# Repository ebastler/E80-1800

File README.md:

# E80-1800
QMK compatible USB-C PCB for a Cherry G80-1800

The board has been prototyped and works as intended, while fitting most G80-1800 housings. Rev 1.1 and later should fix all tolerance issues, and fit all G80-1800 (and as far as I know also G81-1800) enclosures. I can, however, not guarantee perfect operation of the PCB or compatibility with every enclosure variation - if you encounter any issues, please let me know. Rev 1.2 has not yet been tested, but changes were minimal - no issues are to be expected. Stock situations as well as component rotations at JLC may change over time and hence I can not guarantee for the BOM/CPL files to work perfectly. Please double-check before ordering!

|||
|:----------------------------------------:|:----------------------------------------:|

## Order information at JLCPCB
All relevant files can be found in `E80-1800-pcb-universal\jlcpcb`. The `gerber` subfolder contains a .zip file, the `assembly` subfolder contains the BOM and POS/CPL files needed for assembly. Please double-check all component values and rotations before ordering!

* [gerber](E80-1800-pcb-universal/jlcpcb/gerber/GERBER-E80-1800-pcb-universal.zip)
* [BOM](E80-1800-pcb-universal/jlcpcb/assembly/BOM-E80-1800-pcb-universal.csv)
* [POS](E80-1800-pcb-universal/jlcpcb/assembly/POS-E80-1800-pcb-universal.csv)

Since jlcpcb usually fails to auto-determine the PCB dimensions: `382 x 160 mm` is the correct size.

Consider donating me a few bucks if you order boards :)

## Features
 - USB-C (you have to widen the cable hole in the case with a file or similar)
 - Full ESD protection
 - Future-proof STM32F072 with QMK
 - Optional I²C OLED screen in the card-reader-hole on card-reader G80-1800 models
 - SPI header for Bluetooth LE - software support may or may not follow (currently not supported by QMK). The SPI pads can also be used for other expansions such as adding a Solenoid or RGB stripe.
 - Header to connect an optional battery management daughterboard
 - Single color dimmable backlight (3mm LEDs)
 - Silkscreen labels for LED polarity and multi-layout options for easier assembly

The board is fully supported by the QMK master branch: https://github.com/qmk/qmk_firmware/tree/master/keyboards/ebastler/e80_1800
A VIA compatible JSON file can be found in the "VIA" folder of this repo, and the PCB is also fully supported by https://remap-keys.app

## Supported layouts
The PCB was designed to support all layout options G80-1800 and G81-1800 were originally available in. I did not include layout options that go beyond those on purpose, since overlapping switch holes lead to wobbly switches (remember, the G80 boards are plateless!) which diminishes the typing experience. 
 - Full ISO and ANSI support
 - 1 - 1 - 1 - 6 - 1 - 1 - 1 - 1 bottom row (with flipped or regular spacebar)
 - 1.5 - 1.5 - 7 - 1.5 - 1.5 bottom row
 - Stepped and regular caps lock

## Thanks to
 - [Evy](https://github.com/evyd13) for supplying me with her [GH80-1800 drop in replacement PCB](https://geekhack.org/index.php?topic=96692.0) layout, which I could use for dimensions and measurements - saved me a lot of time! Even if I ended up redrawing the dimensions from scratch and changing a few, being able to use his as a starting point was a lot of help.
 - SMOKEY for motivating me once I lost the will to continue with the project
 - MarvFPV for helping me with the physical PCB dimensions and supplying me with valuable ideas
 - Zitres for organizing and shipping a small-batch closed GB together with me that led to a lot of satisfied users

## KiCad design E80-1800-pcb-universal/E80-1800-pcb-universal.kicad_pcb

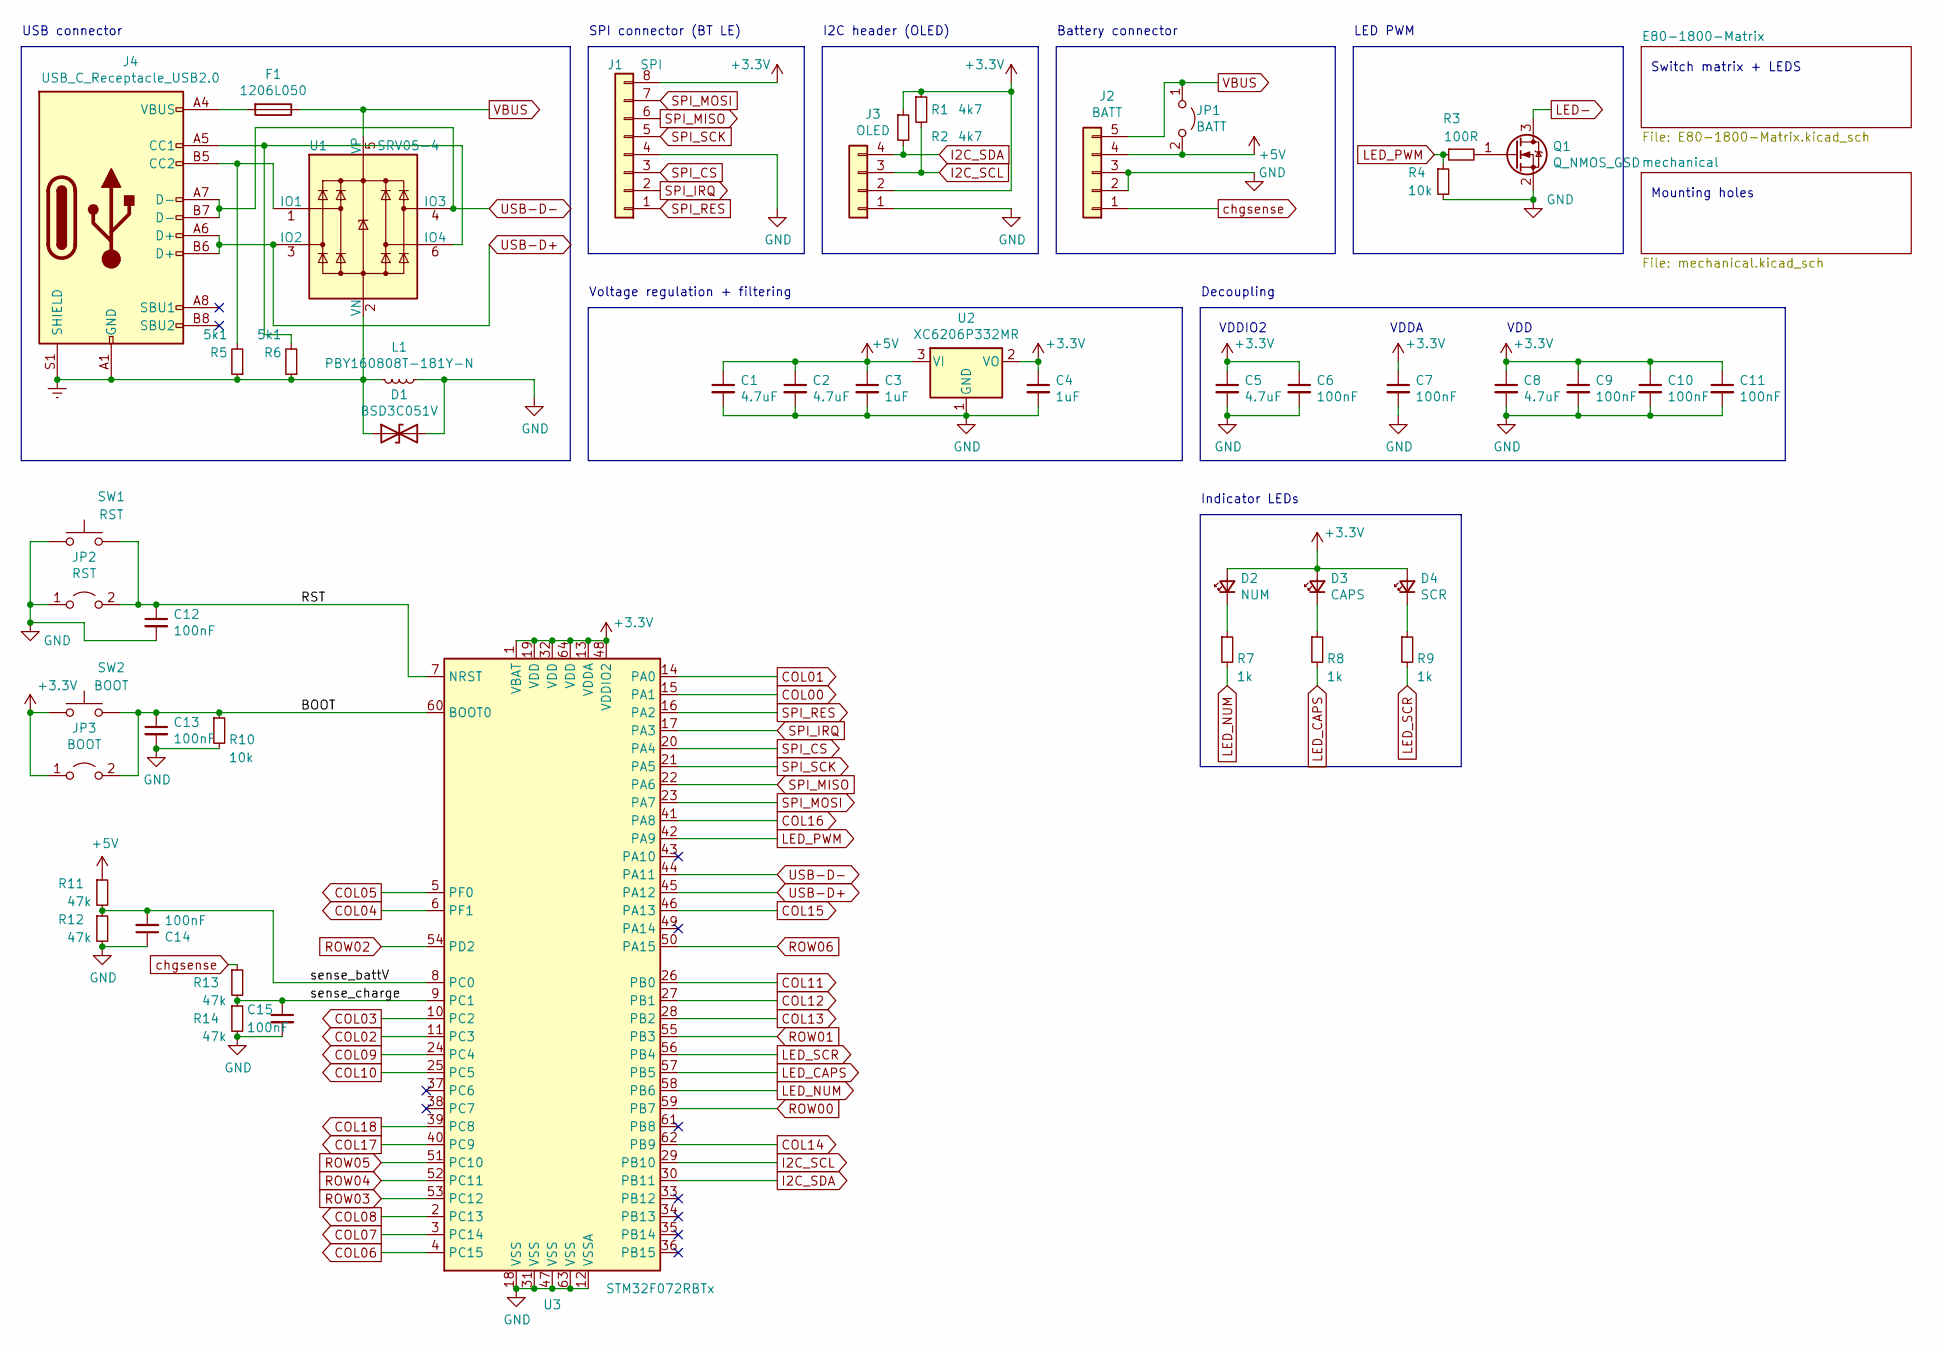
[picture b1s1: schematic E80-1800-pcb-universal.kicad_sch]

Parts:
C1, C2, C5, C8: 4.7uF; C_0603_1608Metric; LCSC C19666
C3, C4: 1uF; C_0603_1608Metric; LCSC C15849
C6, C7, C9, C10, C11, C12, C13, C14, C15: 100nF; C_0603_1608Metric; LCSC C14663
D1: BSD3C051V; D_SOD-323; LCSC C151996
D2: NUM; LED_D3.0mm
D3: CAPS; LED_D3.0mm
D4: SCR; LED_D3.0mm
F1: 1206L050; Fuse_1206_3216Metric; LCSC C151162
J1: SPI; JST_SH_SM08B-SRSS-TB_1x08-1MP_P1.00mm_Horizontal
J2: BATT; JST_SH_SM05B-SRSS-TB_1x05-1MP_P1.00mm_Horizontal
J3: OLED; PinHeader_1x04_P2.54mm_Vertical
J4: USB_C_Receptacle_USB2.0; USB_C_Receptacle_HRO_TYPE-C-31-M-12; LCSC C165948
JP1: BATT; SolderJumper-2_P1.3mm_Bridged2Bar_Pad1.0x1.5mm
JP2: RST; PinHeader_1x02_P2.54mm_Vertical
JP3: BOOT; PinHeader_1x02_P2.54mm_Vertical
L1: PBY160808T-181Y-N; L_0603_1608Metric_Pad1.05x0.95mm_HandSolder; LCSC C114288
Q1: Q_NMOS_GSD; SOT-23; LCSC C20917
R1, R2: 4k7; R_0603_1608Metric; LCSC C23162
R3: 100R; R_0603_1608Metric; LCSC C22775
R4, R10: 10k; R_0603_1608Metric; LCSC C25804
R5, R6: 5k1; R_0603_1608Metric; LCSC C23186
R7, R8, R9: 1k; R_0603_1608Metric; LCSC C21190
R11, R12, R13, R14: 47k; R_0603_1608Metric; LCSC C25819
SW1: RST; SW_SPST_SKQG_WithoutStem
SW2: BOOT; SW_SPST_SKQG_WithoutStem
U1: SRV05-4; SOT-23-6; LCSC C85364
U2: XC6206P332MR; SOT-23; LCSC C5446
U3: STM32F072RBTx; LQFP-64_10x10mm_P0.5mm; LCSC C46046

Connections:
COL00: U3.15 (PA1); also elsewhere on the board
COL01: U3.14 (PA0); also elsewhere on the board
COL02: U3.11 (PC3); also elsewhere on the board
COL03: U3.10 (PC2); also elsewhere on the board
COL04: U3.6 (PF1); also elsewhere on the board
COL05: U3.5 (PF0); also elsewhere on the board
COL06: U3.4 (PC15); also elsewhere on the board
COL07: U3.3 (PC14); also elsewhere on the board
COL08: U3.2 (PC13); also elsewhere on the board
COL09: U3.24 (PC4); also elsewhere on the board
COL10: U3.25 (PC5); also elsewhere on the board
COL11: U3.26 (PB0); also elsewhere on the board
COL12: U3.27 (PB1); also elsewhere on the board
COL13: U3.28 (PB2); also elsewhere on the board
COL14: U3.62 (PB9); also elsewhere on the board
COL15: U3.46 (PA13); also elsewhere on the board
COL16: U3.41 (PA8); also elsewhere on the board
COL17: U3.40 (PC9); also elsewhere on the board
COL18: U3.39 (PC8); also elsewhere on the board
Earth: D1.1 (A1), J4.A1 (GND), J4.A12 (GND), J4.B1 (GND), J4.B12 (GND), J4.S1 (SHIELD), L1.2, R5.1, R6.1, U1.2 (VN)
I2C_SCL: J3.3, R1.2, U3.29 (PB10)
I2C_SDA: J3.4, R2.2, U3.30 (PB11)
LED-: Q1.3 (D); also elsewhere on the board
LED_CAPS: R8.2, U3.57 (PB5)
LED_NUM: R7.2, U3.58 (PB6)
LED_PWM: R3.1, R4.1, U3.42 (PA9)
LED_SCR: R9.2, U3.56 (PB4)
unnamed: D2.1 (K), R7.1
unnamed: D3.1 (K), R8.1
unnamed: D4.1 (K), R9.1
unnamed: F1.2, J4.A4 (VBUS), J4.A9 (VBUS), J4.B4 (VBUS), J4.B9 (VBUS)
unnamed: J4.A5 (CC1), R6.2, U1.6 (IO4)
unnamed: J4.B5 (CC2), R5.2, U1.1 (IO1)
unnamed: Q1.1 (G), R3.2
ROW00: U3.59 (PB7); also elsewhere on the board
ROW01: U3.55 (PB3); also elsewhere on the board
ROW02: U3.54 (PD2); also elsewhere on the board
ROW03: U3.53 (PC12); also elsewhere on the board
ROW04: U3.52 (PC11); also elsewhere on the board
ROW05: U3.51 (PC10); also elsewhere on the board
ROW06: U3.50 (PA15); also elsewhere on the board
SPI_CS: J1.3, U3.20 (PA4)
SPI_IRQ: J1.2, U3.17 (PA3)
SPI_MISO: J1.6, U3.22 (PA6)
SPI_MOSI: J1.7, U3.23 (PA7)
SPI_RES: J1.1, U3.16 (PA2)
SPI_SCK: J1.5, U3.21 (PA5)
USB-D+: J4.A6 (D+), J4.B6 (D+), U1.3 (IO2), U3.45 (PA12)
USB-D-: J4.A7 (D-), J4.B7 (D-), U1.4 (IO3), U3.44 (PA11)
VBUS: F1.1, J2.5, JP1.1 (A), U1.5 (VP)
chgsense: J2.1, R13.1

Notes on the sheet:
Mounting holes
LED PWM
VDDA
SPI connector (BT LE)
VDD
USB connector
I2C header (OLED)
VDDIO2
Indicator LEDs
Voltage regulation + filtering
Switch matrix + LEDS
Decoupling
Battery connector

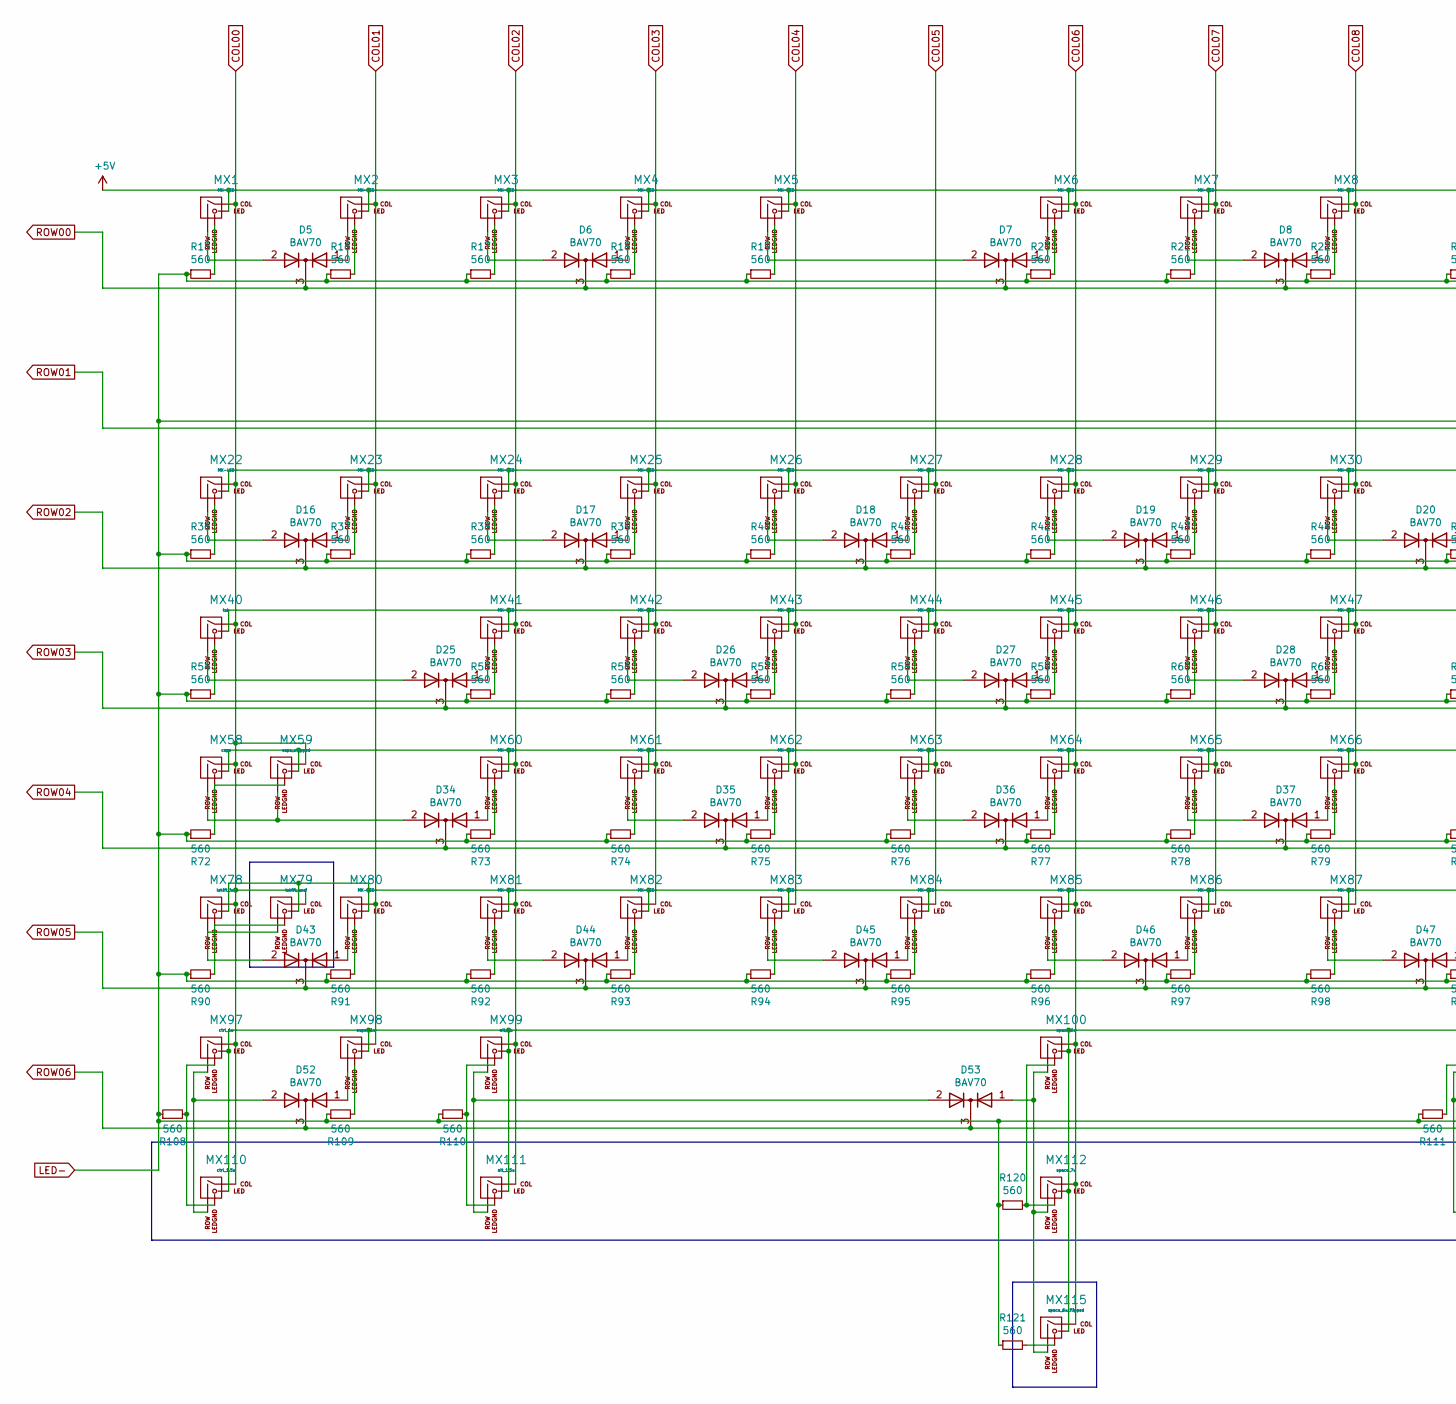
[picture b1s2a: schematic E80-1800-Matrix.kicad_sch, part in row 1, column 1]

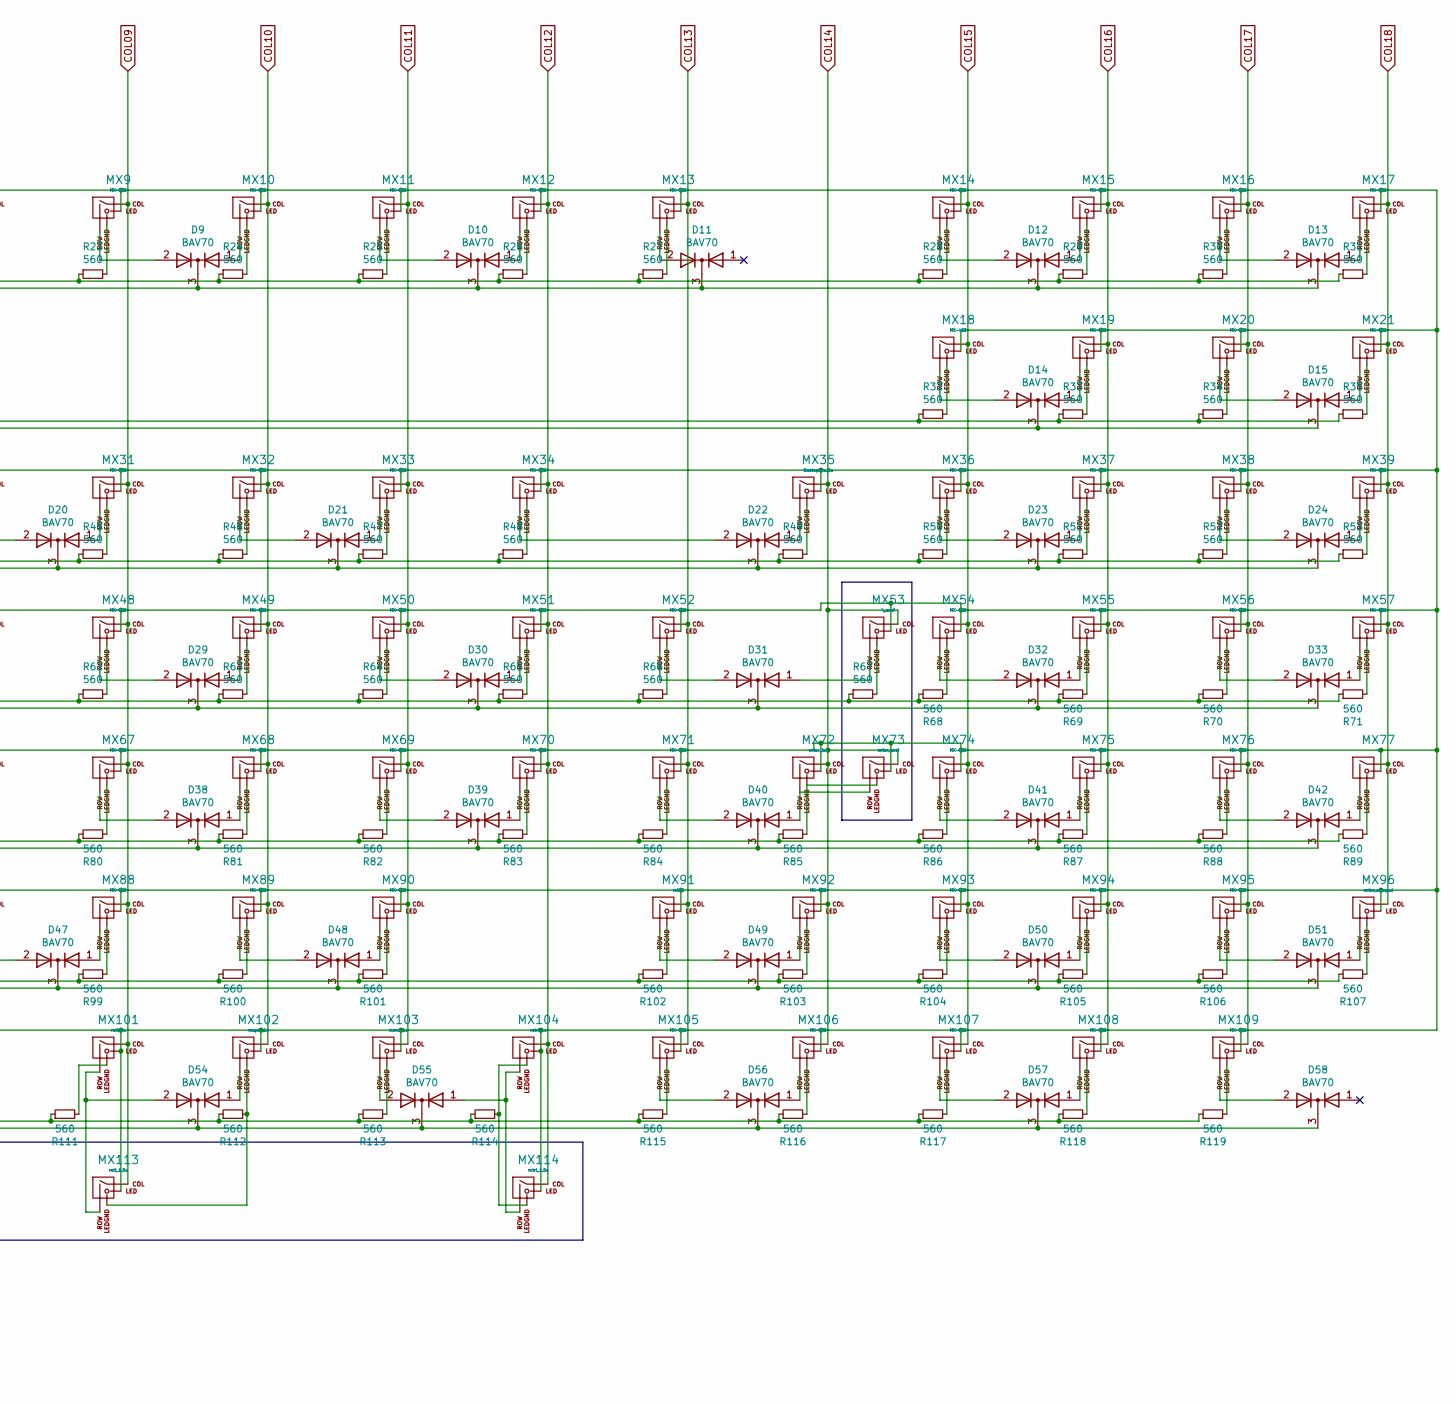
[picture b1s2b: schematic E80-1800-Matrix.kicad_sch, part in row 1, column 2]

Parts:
D5, D6, D7, D8, D9, D10, D11, D12, D13, D14, D15, D16, D17, D18, D19, D20, D21, D22, D23, D24, D25, D26, D27, D28, D29, D30, D31, D32, D33, D34, D35, D36, D37, D38, D39, D40, D41, D42, D43, D44, D45, D46, D47, D48, D49, D50, D51, D52, D53, D54, D55, D56, D57, D58: BAV70; SOT-23; LCSC C68978
MX1, MX2, MX3, MX4, MX5, MX6, MX7, MX8, MX9, MX10, MX11, MX12, MX13, MX14, MX15, MX16, MX17, MX18, MX19, MX20, MX21, MX22, MX23, MX24, MX25, MX26, MX27, MX28, MX29, MX30, MX31, MX32, MX33, MX34, MX36, MX37, MX38, MX39, MX41, MX42, MX43, MX44, MX45, MX46, MX47, MX48, MX49, MX50, MX51, MX52, MX54, MX55, MX56, MX57, MX60, MX61, MX62, MX63, MX64, MX65, MX66, MX67, MX68, MX69, MX70, MX71, MX74, MX75, MX76, MX80, MX81, MX82, MX83, MX84, MX85, MX86, MX87, MX88, MX89, MX90, MX92, MX93, MX94, MX95, MX105, MX106, MX107, MX108, MX109: MX-LED; MXOnly-1U
MX35: Backspace_2u; MXOnly-2U
MX40: tab; MXOnly-1.5U
MX53: \_ansi; MXOnly-1.5U
MX58: caps; MXOnly-1.75U-FLIPPED
MX59: caps_stepped; MXOnly-1.25U
MX72: enter_iso; MXOnly-ISO-ROTATED-ReversedStabilizers
MX73: enter_ansi; MXOnly-2.25U
MX77: +; MXOnly-1U
MX78: lshift_iso; MXOnly-1.25U
MX79: lshift_ansi; MXOnly-2.25U
MX91: rshift; MXOnly-1.75U
MX96: enter_numpad; MXOnly-ISO
MX97: ctrl_1u; MXOnly-1U
MX98: super_1u; MXOnly-1U
MX99: alt_1u; MXOnly-1U-FLIPPED
MX100: space_6u; MXOnly-6U
MX101: ralt_1u; MXOnly-1U
MX102: rsuper_1u; MXOnly-1U
MX103: menu_1u; MXOnly-1U
MX104: rctrl_1u; MXOnly-1U-FLIPPED
MX110: ctrl_1.5u; MXOnly-1.5U-FLIPPED
MX111: alt_1.5u; MXOnly-1.5U
MX112: space_7u; MXOnly-7U
MX113: ralt_1.5u; MXOnly-1.5U-FLIPPED
MX114: rctrl_1.5u; MXOnly-1.5U
MX115: space_6u_flipped; MXOnly-1U
R15, R16, R17, R18, R19, R20, R21, R22, R23, R24, R25, R26, R27, R28, R29, R30, R31, R32, R33, R34, R35, R36, R37, R38, R39, R40, R41, R42, R43, R44, R45, R46, R47, R48, R49, R50, R51, R52, R53, R54, R55, R56, R57, R58, R59, R60, R61, R62, R63, R64, R65, R66, R67, R68, R69, R70, R71, R72, R73, R74, R75, R76, R77, R78, R79, R80, R81, R82, R83, R84, R85, R86, R87, R88, R89, R90, R91, R92, R93, R94, R95, R96, R97, R98, R99, R100, R101, R102, R103, R104, R105, R106, R107, R108, R109, R110, R111, R112, R113, R114, R115, R116, R117, R118, R119, R120, R121: 560; R_0603_1608Metric; LCSC C23204

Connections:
COL00: MX1.1 (COL), MX22.1 (COL), MX40.1 (COL), MX58.1 (COL), MX59.1 (COL), MX78.1 (COL), MX79.1 (COL), MX97.1 (COL), MX110.1 (COL); also elsewhere on the board
COL01: MX2.1 (COL), MX23.1 (COL), MX80.1 (COL), MX98.1 (COL); also elsewhere on the board
COL02: MX3.1 (COL), MX24.1 (COL), MX41.1 (COL), MX60.1 (COL), MX81.1 (COL), MX99.1 (COL), MX111.1 (COL); also elsewhere on the board
COL03: MX4.1 (COL), MX25.1 (COL), MX42.1 (COL), MX61.1 (COL), MX82.1 (COL); also elsewhere on the board
COL04: MX5.1 (COL), MX26.1 (COL), MX43.1 (COL), MX62.1 (COL), MX83.1 (COL); also elsewhere on the board
COL05: MX27.1 (COL), MX44.1 (COL), MX63.1 (COL), MX84.1 (COL); also elsewhere on the board
COL06: MX6.1 (COL), MX28.1 (COL), MX45.1 (COL), MX64.1 (COL), MX85.1 (COL), MX100.1 (COL), MX112.1 (COL), MX115.1 (COL); also elsewhere on the board
COL07: MX7.1 (COL), MX29.1 (COL), MX46.1 (COL), MX65.1 (COL), MX86.1 (COL); also elsewhere on the board
COL08: MX8.1 (COL), MX30.1 (COL), MX47.1 (COL), MX66.1 (COL), MX87.1 (COL); also elsewhere on the board
COL09: MX9.1 (COL), MX31.1 (COL), MX48.1 (COL), MX67.1 (COL), MX88.1 (COL), MX101.1 (COL), MX113.1 (COL); also elsewhere on the board
COL10: MX10.1 (COL), MX32.1 (COL), MX49.1 (COL), MX68.1 (COL), MX89.1 (COL), MX102.1 (COL); also elsewhere on the board
COL11: MX11.1 (COL), MX33.1 (COL), MX50.1 (COL), MX69.1 (COL), MX90.1 (COL), MX103.1 (COL); also elsewhere on the board
COL12: MX12.1 (COL), MX34.1 (COL), MX51.1 (COL), MX70.1 (COL), MX104.1 (COL), MX114.1 (COL); also elsewhere on the board
COL13: MX13.1 (COL), MX52.1 (COL), MX71.1 (COL), MX91.1 (COL), MX105.1 (COL); also elsewhere on the board
COL14: MX35.1 (COL), MX53.1 (COL), MX72.1 (COL), MX73.1 (COL), MX92.1 (COL), MX106.1 (COL); also elsewhere on the board
COL15: MX14.1 (COL), MX18.1 (COL), MX36.1 (COL), MX54.1 (COL), MX74.1 (COL), MX93.1 (COL), MX107.1 (COL); also elsewhere on the board
COL16: MX15.1 (COL), MX19.1 (COL), MX37.1 (COL), MX55.1 (COL), MX75.1 (COL), MX94.1 (COL), MX108.1 (COL); also elsewhere on the board
COL17: MX16.1 (COL), MX20.1 (COL), MX38.1 (COL), MX56.1 (COL), MX76.1 (COL), MX95.1 (COL), MX109.1 (COL); also elsewhere on the board
COL18: MX17.1 (COL), MX21.1 (COL), MX39.1 (COL), MX57.1 (COL), MX77.1 (COL), MX96.1 (COL); also elsewhere on the board
LED-: R15.1, R16.1, R17.1, R18.1, R19.1, R20.1, R21.1, R22.1, R23.1, R24.1, R25.1, R26.1, R27.1, R28.1, R29.1, R30.1, R31.1, R32.1, R33.1, R34.1, R35.1, R36.1, R37.1, R38.1, R39.1, R40.1, R41.1, R42.1, R43.1, R44.1, R45.1, R46.1, R47.1, R48.1, R49.1, R50.1, R51.1, R52.1, R53.1, R54.1, R55.1, R56.1, R57.1, R58.1, R59.1, R60.1, R61.1, R62.1, R63.1, R64.1, R65.1, R66.1, R67.1, R68.1, R69.1, R70.1, R71.1, R72.1, R73.1, R74.1, R75.1, R76.1, R77.1, R78.1, R79.1, R80.1, R81.1, R82.1, R83.1, R84.1, R85.1, R86.1, R87.1, R88.1, R89.1, R90.1, R91.1, R92.1, R93.1, R94.1, R95.1, R96.1, R97.1, R98.1, R99.1, R100.1, R101.1, R102.1, R103.1, R104.1, R105.1, R106.1, R107.1, R108.1, R109.1, R110.1, R111.1, R112.1, R113.1, R114.1, R115.1, R116.1, R117.1, R118.1, R119.1, R120.1, R121.1; also elsewhere on the board
unnamed: D5.1 (A), MX2.2 (ROW)
unnamed: D5.2 (A), MX1.2 (ROW)
unnamed: D6.1 (A), MX4.2 (ROW)
unnamed: D6.2 (A), MX3.2 (ROW)
unnamed: D7.1 (A), MX6.2 (ROW)
unnamed: D7.2 (A), MX5.2 (ROW)
unnamed: D8.1 (A), MX8.2 (ROW)
unnamed: D8.2 (A), MX7.2 (ROW)
unnamed: D9.1 (A), MX10.2 (ROW)
unnamed: D9.2 (A), MX9.2 (ROW)
unnamed: D10.1 (A), MX12.2 (ROW)
unnamed: D10.2 (A), MX11.2 (ROW)
unnamed: D11.2 (A), MX13.2 (ROW)
unnamed: D12.1 (A), MX15.2 (ROW)
unnamed: D12.2 (A), MX14.2 (ROW)
unnamed: D13.1 (A), MX17.2 (ROW)
unnamed: D13.2 (A), MX16.2 (ROW)
unnamed: D14.1 (A), MX19.2 (ROW)
unnamed: D14.2 (A), MX18.2 (ROW)
unnamed: D15.1 (A), MX21.2 (ROW)
unnamed: D15.2 (A), MX20.2 (ROW)
unnamed: D16.1 (A), MX23.2 (ROW)
unnamed: D16.2 (A), MX22.2 (ROW)
unnamed: D17.1 (A), MX25.2 (ROW)
unnamed: D17.2 (A), MX24.2 (ROW)
unnamed: D18.1 (A), MX27.2 (ROW)
unnamed: D18.2 (A), MX26.2 (ROW)
unnamed: D19.1 (A), MX29.2 (ROW)
unnamed: D19.2 (A), MX28.2 (ROW)
unnamed: D20.1 (A), MX31.2 (ROW)
unnamed: D20.2 (A), MX30.2 (ROW)
unnamed: D21.1 (A), MX33.2 (ROW)
unnamed: D21.2 (A), MX32.2 (ROW)
unnamed: D22.1 (A), MX35.2 (ROW)
unnamed: D22.2 (A), MX34.2 (ROW)
unnamed: D23.1 (A), MX37.2 (ROW)
unnamed: D23.2 (A), MX36.2 (ROW)
unnamed: D24.1 (A), MX39.2 (ROW)
unnamed: D24.2 (A), MX38.2 (ROW)
unnamed: D25.1 (A), MX41.2 (ROW)
unnamed: D25.2 (A), MX40.2 (ROW)
unnamed: D26.1 (A), MX43.2 (ROW)
unnamed: D26.2 (A), MX42.2 (ROW)
unnamed: D27.1 (A), MX45.2 (ROW)
unnamed: D27.2 (A), MX44.2 (ROW)
unnamed: D28.1 (A), MX47.2 (ROW)
unnamed: D28.2 (A), MX46.2 (ROW)
unnamed: D29.1 (A), MX49.2 (ROW)
unnamed: D29.2 (A), MX48.2 (ROW)
unnamed: D30.1 (A), MX51.2 (ROW)
unnamed: D30.2 (A), MX50.2 (ROW)
unnamed: D31.1 (A), MX53.2 (ROW)
unnamed: D31.2 (A), MX52.2 (ROW)
unnamed: D32.1 (A), MX55.2 (ROW)
unnamed: D32.2 (A), MX54.2 (ROW)
unnamed: D33.1 (A), MX57.2 (ROW)
unnamed: D33.2 (A), MX56.2 (ROW)
unnamed: D34.1 (A), MX60.2 (ROW)
unnamed: D34.2 (A), MX58.2 (ROW), MX59.2 (ROW)
unnamed: D35.1 (A), MX62.2 (ROW)
unnamed: D35.2 (A), MX61.2 (ROW)
unnamed: D36.1 (A), MX64.2 (ROW)
unnamed: D36.2 (A), MX63.2 (ROW)
unnamed: D37.1 (A), MX66.2 (ROW)
unnamed: D37.2 (A), MX65.2 (ROW)
unnamed: D38.1 (A), MX68.2 (ROW)
unnamed: D38.2 (A), MX67.2 (ROW)
unnamed: D39.1 (A), MX70.2 (ROW)
unnamed: D39.2 (A), MX69.2 (ROW)
unnamed: D40.1 (A), MX72.2 (ROW), MX73.2 (ROW)
unnamed: D40.2 (A), MX71.2 (ROW)
unnamed: D41.1 (A), MX75.2 (ROW)
unnamed: D41.2 (A), MX74.2 (ROW)
unnamed: D42.1 (A), MX77.2 (ROW)
unnamed: D42.2 (A), MX76.2 (ROW)
unnamed: D43.1 (A), MX80.2 (ROW)
unnamed: D43.2 (A), MX78.2 (ROW), MX79.2 (ROW)
unnamed: D44.1 (A), MX82.2 (ROW)
unnamed: D44.2 (A), MX81.2 (ROW)
unnamed: D45.1 (A), MX84.2 (ROW)
unnamed: D45.2 (A), MX83.2 (ROW)
unnamed: D46.1 (A), MX86.2 (ROW)
unnamed: D46.2 (A), MX85.2 (ROW)
unnamed: D47.1 (A), MX88.2 (ROW)
unnamed: D47.2 (A), MX87.2 (ROW)
unnamed: D48.1 (A), MX90.2 (ROW)
unnamed: D48.2 (A), MX89.2 (ROW)
unnamed: D49.1 (A), MX92.2 (ROW)
unnamed: D49.2 (A), MX91.2 (ROW)
unnamed: D50.1 (A), MX94.2 (ROW)
unnamed: D50.2 (A), MX93.2 (ROW)
unnamed: D51.1 (A), MX96.2 (ROW)
unnamed: D51.2 (A), MX95.2 (ROW)
unnamed: D52.1 (A), MX98.2 (ROW)
unnamed: D52.2 (A), MX97.2 (ROW), MX110.2 (ROW)
unnamed: D53.1 (A), MX100.2 (ROW), MX112.2 (ROW), MX115.2 (ROW)
unnamed: D53.2 (A), MX99.2 (ROW), MX111.2 (ROW)
unnamed: D54.1 (A), MX102.2 (ROW)
unnamed: D54.2 (A), MX101.2 (ROW), MX113.2 (ROW)
unnamed: D55.1 (A), MX104.2 (ROW), MX114.2 (ROW)
unnamed: D55.2 (A), MX103.2 (ROW)
unnamed: D56.1 (A), MX106.2 (ROW)
unnamed: D56.2 (A), MX105.2 (ROW)
unnamed: D57.1 (A), MX108.2 (ROW)
unnamed: D57.2 (A), MX107.2 (ROW)
unnamed: D58.2 (A), MX109.2 (ROW)
unnamed: MX1.4 (LEDGND), R15.2
unnamed: MX2.4 (LEDGND), R16.2
unnamed: MX3.4 (LEDGND), R17.2
unnamed: MX4.4 (LEDGND), R18.2
unnamed: MX5.4 (LEDGND), R19.2
unnamed: MX6.4 (LEDGND), R20.2
unnamed: MX7.4 (LEDGND), R21.2
unnamed: MX8.4 (LEDGND), R22.2
unnamed: MX9.4 (LEDGND), R23.2
unnamed: MX10.4 (LEDGND), R24.2
unnamed: MX11.4 (LEDGND), R25.2
unnamed: MX12.4 (LEDGND), R26.2
unnamed: MX13.4 (LEDGND), R27.2
unnamed: MX14.4 (LEDGND), R28.2
unnamed: MX15.4 (LEDGND), R29.2
unnamed: MX16.4 (LEDGND), R30.2
unnamed: MX17.4 (LEDGND), R31.2
unnamed: MX18.4 (LEDGND), R32.2
unnamed: MX19.4 (LEDGND), R33.2
unnamed: MX20.4 (LEDGND), R34.2
unnamed: MX21.4 (LEDGND), R35.2
unnamed: MX22.4 (LEDGND), R36.2
unnamed: MX23.4 (LEDGND), R37.2
unnamed: MX24.4 (LEDGND), R38.2
unnamed: MX25.4 (LEDGND), R39.2
unnamed: MX26.4 (LEDGND), R40.2
unnamed: MX27.4 (LEDGND), R41.2
unnamed: MX28.4 (LEDGND), R42.2
unnamed: MX29.4 (LEDGND), R43.2
unnamed: MX30.4 (LEDGND), R44.2
unnamed: MX31.4 (LEDGND), R45.2
unnamed: MX32.4 (LEDGND), R46.2
unnamed: MX33.4 (LEDGND), R47.2
unnamed: MX34.4 (LEDGND), R48.2
unnamed: MX35.4 (LEDGND), R49.2
unnamed: MX36.4 (LEDGND), R50.2
unnamed: MX37.4 (LEDGND), R51.2
unnamed: MX38.4 (LEDGND), R52.2
unnamed: MX39.4 (LEDGND), R53.2
unnamed: MX40.4 (LEDGND), R54.2
unnamed: MX41.4 (LEDGND), R55.2
unnamed: MX42.4 (LEDGND), R56.2
unnamed: MX43.4 (LEDGND), R57.2
unnamed: MX44.4 (LEDGND), R58.2
unnamed: MX45.4 (LEDGND), R59.2
unnamed: MX46.4 (LEDGND), R60.2
unnamed: MX47.4 (LEDGND), R61.2
unnamed: MX48.4 (LEDGND), R62.2
unnamed: MX49.4 (LEDGND), R63.2
unnamed: MX50.4 (LEDGND), R64.2
unnamed: MX51.4 (LEDGND), R65.2
unnamed: MX52.4 (LEDGND), R66.2
unnamed: MX53.4 (LEDGND), R67.2
unnamed: MX54.4 (LEDGND), R68.2
unnamed: MX55.4 (LEDGND), R69.2
unnamed: MX56.4 (LEDGND), R70.2
unnamed: MX57.4 (LEDGND), R71.2
unnamed: MX58.4 (LEDGND), MX59.4 (LEDGND), R72.2
unnamed: MX60.4 (LEDGND), R73.2
unnamed: MX61.4 (LEDGND), R74.2
unnamed: MX62.4 (LEDGND), R75.2
unnamed: MX63.4 (LEDGND), R76.2
unnamed: MX64.4 (LEDGND), R77.2
unnamed: MX65.4 (LEDGND), R78.2
unnamed: MX66.4 (LEDGND), R79.2
unnamed: MX67.4 (LEDGND), R80.2
unnamed: MX68.4 (LEDGND), R81.2
unnamed: MX69.4 (LEDGND), R82.2
unnamed: MX70.4 (LEDGND), R83.2
unnamed: MX71.4 (LEDGND), R84.2
unnamed: MX72.4 (LEDGND), MX73.4 (LEDGND), R85.2
unnamed: MX74.4 (LEDGND), R86.2
unnamed: MX75.4 (LEDGND), R87.2
unnamed: MX76.4 (LEDGND), R88.2
unnamed: MX77.4 (LEDGND), R89.2
unnamed: MX78.4 (LEDGND), MX79.4 (LEDGND), R90.2
unnamed: MX80.4 (LEDGND), R91.2
unnamed: MX81.4 (LEDGND), R92.2
unnamed: MX82.4 (LEDGND), R93.2
unnamed: MX83.4 (LEDGND), R94.2
unnamed: MX84.4 (LEDGND), R95.2
unnamed: MX85.4 (LEDGND), R96.2
unnamed: MX86.4 (LEDGND), R97.2
unnamed: MX87.4 (LEDGND), R98.2
unnamed: MX88.4 (LEDGND), R99.2
unnamed: MX89.4 (LEDGND), R100.2
unnamed: MX90.4 (LEDGND), R101.2
unnamed: MX91.4 (LEDGND), R102.2
unnamed: MX92.4 (LEDGND), R103.2
unnamed: MX93.4 (LEDGND), R104.2
unnamed: MX94.4 (LEDGND), R105.2
unnamed: MX95.4 (LEDGND), R106.2
unnamed: MX96.4 (LEDGND), R107.2
unnamed: MX98.4 (LEDGND), R109.2
unnamed: MX100.4 (LEDGND), MX112.4 (LEDGND), R120.2
unnamed: MX101.4 (LEDGND), R111.2
unnamed: MX102.4 (LEDGND), MX113.4 (LEDGND), R112.2
unnamed: MX103.4 (LEDGND), R113.2
unnamed: MX104.4 (LEDGND), MX114.4 (LEDGND), R114.2
unnamed: MX105.4 (LEDGND), R115.2
unnamed: MX106.4 (LEDGND), R116.2
unnamed: MX107.4 (LEDGND), R117.2
unnamed: MX108.4 (LEDGND), R118.2
unnamed: MX109.4 (LEDGND), R119.2
unnamed: MX97.4 (LEDGND), MX110.4 (LEDGND), R108.2
unnamed: MX99.4 (LEDGND), MX111.4 (LEDGND), R110.2
unnamed: MX115.4 (LEDGND), R121.2
ROW00: D5.3 (K), D6.3 (K), D7.3 (K), D8.3 (K), D9.3 (K), D10.3 (K), D11.3 (K), D12.3 (K), D13.3 (K); also elsewhere on the board
ROW01: D14.3 (K), D15.3 (K); also elsewhere on the board
ROW02: D16.3 (K), D17.3 (K), D18.3 (K), D19.3 (K), D20.3 (K), D21.3 (K), D22.3 (K), D23.3 (K), D24.3 (K); also elsewhere on the board
ROW03: D25.3 (K), D26.3 (K), D27.3 (K), D28.3 (K), D29.3 (K), D30.3 (K), D31.3 (K), D32.3 (K), D33.3 (K); also elsewhere on the board
ROW04: D34.3 (K), D35.3 (K), D36.3 (K), D37.3 (K), D38.3 (K), D39.3 (K), D40.3 (K), D41.3 (K), D42.3 (K); also elsewhere on the board
ROW05: D43.3 (K), D44.3 (K), D45.3 (K), D46.3 (K), D47.3 (K), D48.3 (K), D49.3 (K), D50.3 (K), D51.3 (K); also elsewhere on the board
ROW06: D52.3 (K), D53.3 (K), D54.3 (K), D55.3 (K), D56.3 (K), D57.3 (K), D58.3 (K); also elsewhere on the board

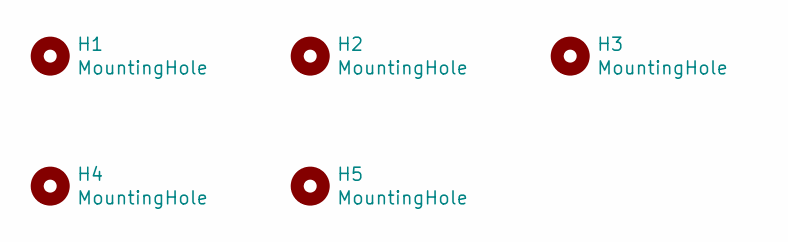
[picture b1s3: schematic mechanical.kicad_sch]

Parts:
H1, H2, H3: MountingHole; MountingHole_6mm
H4, H5: MountingHole; MountingHole_4mm

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
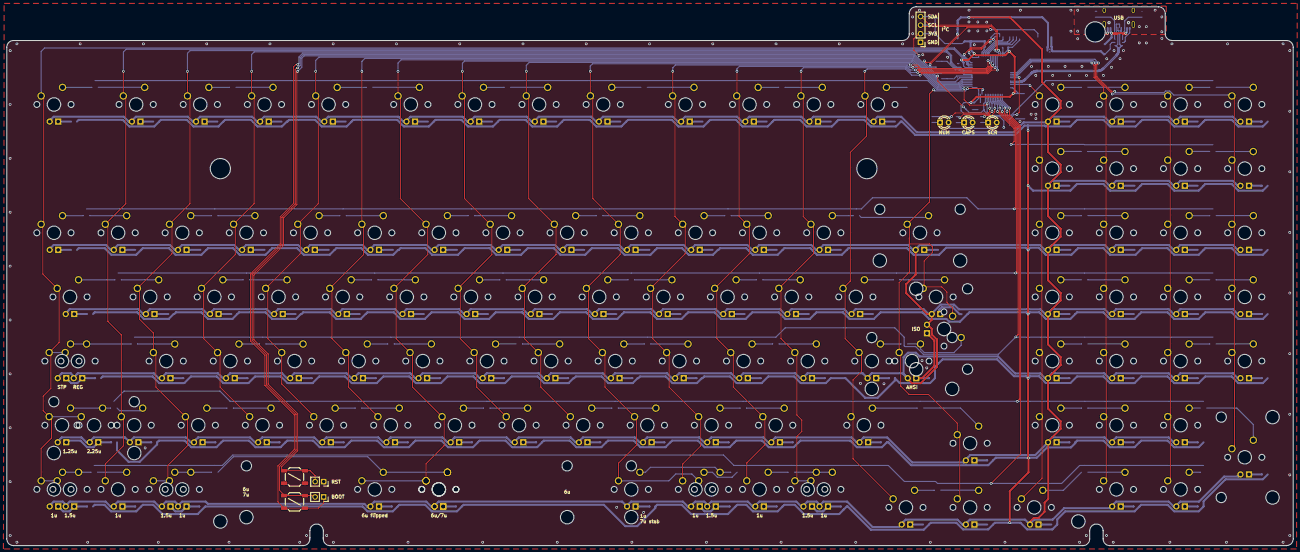
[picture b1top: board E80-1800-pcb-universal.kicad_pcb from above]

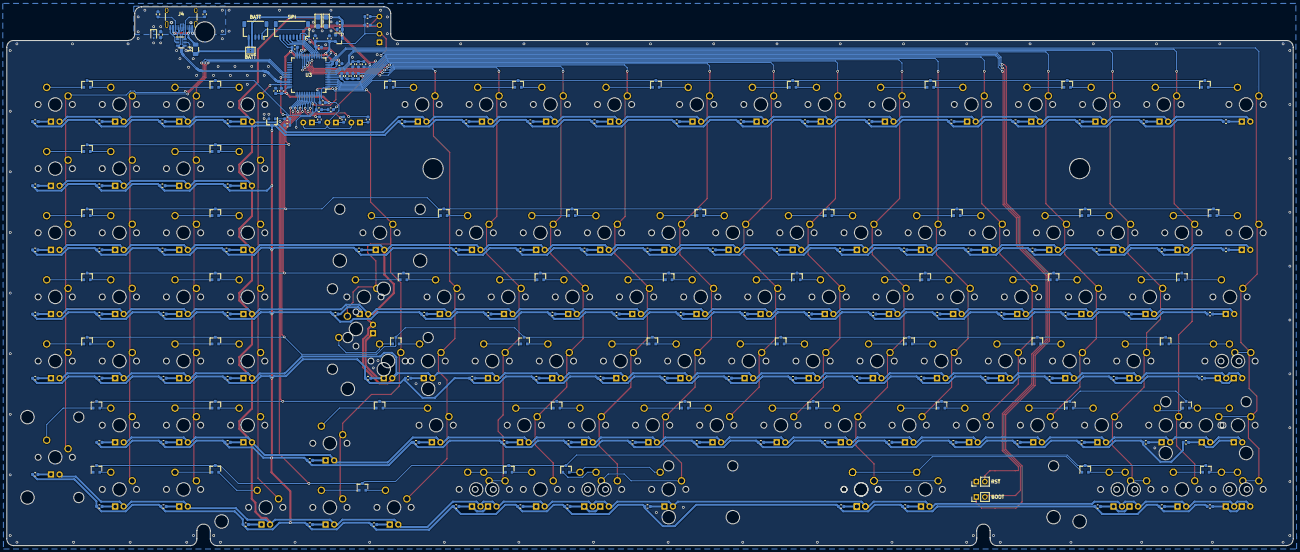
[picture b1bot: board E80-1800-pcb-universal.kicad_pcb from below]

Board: 2 copper layers, 382.0 x 160.0 mm, 330 parts (204 on the bottom side), 271 nets.

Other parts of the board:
C16: 100nF; C_0603_1608Metric_stealth

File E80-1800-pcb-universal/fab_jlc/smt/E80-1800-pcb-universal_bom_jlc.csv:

"Comment","Designator","Footprint","LCSC Part #"
"10uF","C2,C1","CP_EIA-3216-18_Kemet-A_stealth","C7171"
"1uF","C5,C3","C_0603_1608Metric_stealth","C15849"
"4.7uF","C9,C4,C6","C_0603_1608Metric_stealth","C19666"
"100nF","C16,C11,C12,C8,C7,C14,C15,C10,C13","C_0603_1608Metric_stealth","C14663"
"BSD3C051V","D1","D_SOD-323","C151996"
"BAV70","D5,D6,D7,D9,D10,D11,D12,D13,D14,D15,D24,D23,D22,D21,D20,D19,D18,D17,D16,D32,D31,D29,D28,D27,D26,D25,D33,D42,D41,D40,D30,D39,D38,D37,D36,D35,D34,D51,D50,D49,D48,D47,D46,D45,D44,D43,D58,D57,D56,D55,D54,D53,D52,D8","SOT-23_stealth","C68978"
"SCF075-1206R","F1","Fuse_1206_3216Metric_Pad1.42x1.75mm_HandSolder","C183290"
"PBY160808T-181Y-N","L1","L_0603_1608Metric_Pad1.05x0.95mm_HandSolder","C114288"
"AO3400A","Q1","SOT-23_stealth","C20917"
"4k7","R2,R1","R_0603_1608Metric_stealth","C23162"
"100R","R3","R_0603_1608Metric_stealth","C22775"
"5k1","R5,R6","R_0603_1608Metric_stealth","C23186"
"1k","R7,R8,R9","R_0603_1608Metric_stealth","C21190"
"10k","R10,R4","R_0603_1608Metric_stealth","C25804"
"47k","R14,R13,R11,R12","R_0603_1608Metric_stealth","C25819"
"560","R16,R15,R17,R18,R19,R20,R21,R22,R23,R24,R25,R26,R27,R28,R29,R30,R31,R36,R37,R38,R39,R40,R41,R42,R43,R44,R45,R46,R47,R48,R49,R50,R51,R52,R53,R34,R35,R33,R32,R120,R121,R54,R55,R56,R57,R58,R59,R60,R61,R62,R63,R64,R65,R66,R67,R68,R69,R70,R71,R88,R87,R86,R89,R107,R106,R105,R104,R119,R118,R117,R85,R84,R83,R82,R81,R80,R79,R78,R77,R76,R75,R74,R73,R72,R103,R102,R101,R100,R99,R98,R97,R96,R95,R94,R93,R92,R91,R90,R116,R115,R113,R112,R111,R114,R110,R109,R108","R_0603_1608Metric_stealth","C23204"
"SRV05-4","U1","SOT-23-6","C85364"
"XC6206P332MR","U2","SOT-23_stealth","C5446"
"STM32F072RBTx","U3","LQFP-64_10x10mm_P0.5mm","C46046"

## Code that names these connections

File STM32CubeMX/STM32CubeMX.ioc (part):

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Mcu.Name=STM32F072R(8-B)Tx
Mcu.Package=LQFP64
Mcu.UserName=STM32F072RBTx
PA11.Mode=Device
PA11.Signal=USB_DM
PA12.Mode=Device
PA12.Signal=USB_DP
PA2.Signal=GPIO_Output
PA3.Signal=GPIO_Output
PA4.Signal=GPIO_Output
PA5.Signal=SPI1_SCK
PA6.Signal=SPI1_MISO
PA7.Signal=SPI1_MOSI
PA8.Signal=S_TIM1_CH1
PB6.Mode=I2C
PB6.Signal=I2C1_SCL
PB7.Mode=I2C
PB7.Signal=I2C1_SDA
PC0.Mode=IN10
PC0.Signal=ADC_IN10
PC1.Mode=IN11
PC1.Signal=ADC_IN11
board=custom

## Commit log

2020-05-25 Add submodules
2020-05-25 added libs to kicad
2020-06-28 added correct name in license file
2020-06-28 added basic IO to check for pinout conflicts
2020-06-28 created PCB
2020-06-28 wired up remaining cols
2020-06-29 added huge silkscreen pads for "white" front on green pcbs
2020-06-29 temporary gerbers to check on silkscreen
2020-06-30 continued routing
2020-07-04 finished pcb layout, added silk labels
2020-07-04 deleted temporary gerbers
2020-07-04 added jlc gerbers + smt files
2020-07-04 updated readme with pictures
2020-07-20 added real pictures of pcb
2020-07-21 updated status
2020-08-03 added temporary firmware repo
2020-08-31 improved mounting holes
2020-08-31 Removed submodule
2020-08-31 minor routing changes
2020-09-20 cosmethic changes
2020-09-22 added logo submodule
2020-09-22 fixed logo folder
2020-09-22 added logo
2020-09-22 updated submodules
2020-09-22 increased readability, added missing cap
2020-09-22 minor routing improvements, added missing cap
2020-09-22 moved 4u7 to a better spot
2020-09-22 re-added logo
2020-09-22 removed wrongly placed sch text
2020-09-22 removed unneeded 3d model
2020-09-22 updated description
2020-09-22 rephrased a sentence
2020-09-22 moved graphics
2020-10-04 added TVS for ESD prot
2020-10-04 minor routing changes, exposed copper for usb traces, added TVS
2020-10-04 removed backup files
2020-10-04 swapped parts to fit jlc stocks
2020-10-04 added new jlc fab files
2020-10-04 some kicad files
2020-10-04 added warning
2020-10-04 added pcb renders
2020-12-17 added VIA json
2021-03-11 updated kicad cpl/bom to match current stocks, cleaned some unneeded files
2021-03-11 added gitignore
2022-01-12 updated gitignore for kc6.0
2022-01-12 updated to kc6.0 files, minor improvements, new jlcpcb files
2022-01-12 replaced pcb renders
2022-01-12 fixed bom/cpl
2022-07-08 updated to v1.2 (switch to marbastlib)
2022-07-08 fixed gitignore not to exclude BOM/CPL anymore
2022-07-08 fixed gerber path
2022-07-08 added donation line
2022-08-12 corrected rotations after jlcpcb seems to have messed up their entire lib
2024-09-24 update to PCM marbastlib and KC8
2024-09-24 updated jlc production files to current stocks, fixed rotations, moved symbols to PCB marbastlib
